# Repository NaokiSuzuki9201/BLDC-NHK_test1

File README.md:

# BLDC-NHK_test1
NHKに向けて製作していたBLDCMD用の基板です。

## 使用素子
・DRV8300D(ゲートドライブ)  
・ACS710(電流検出素子、絶縁)  
・TLP250H?(TP5, LF5?表面実装のやつ)

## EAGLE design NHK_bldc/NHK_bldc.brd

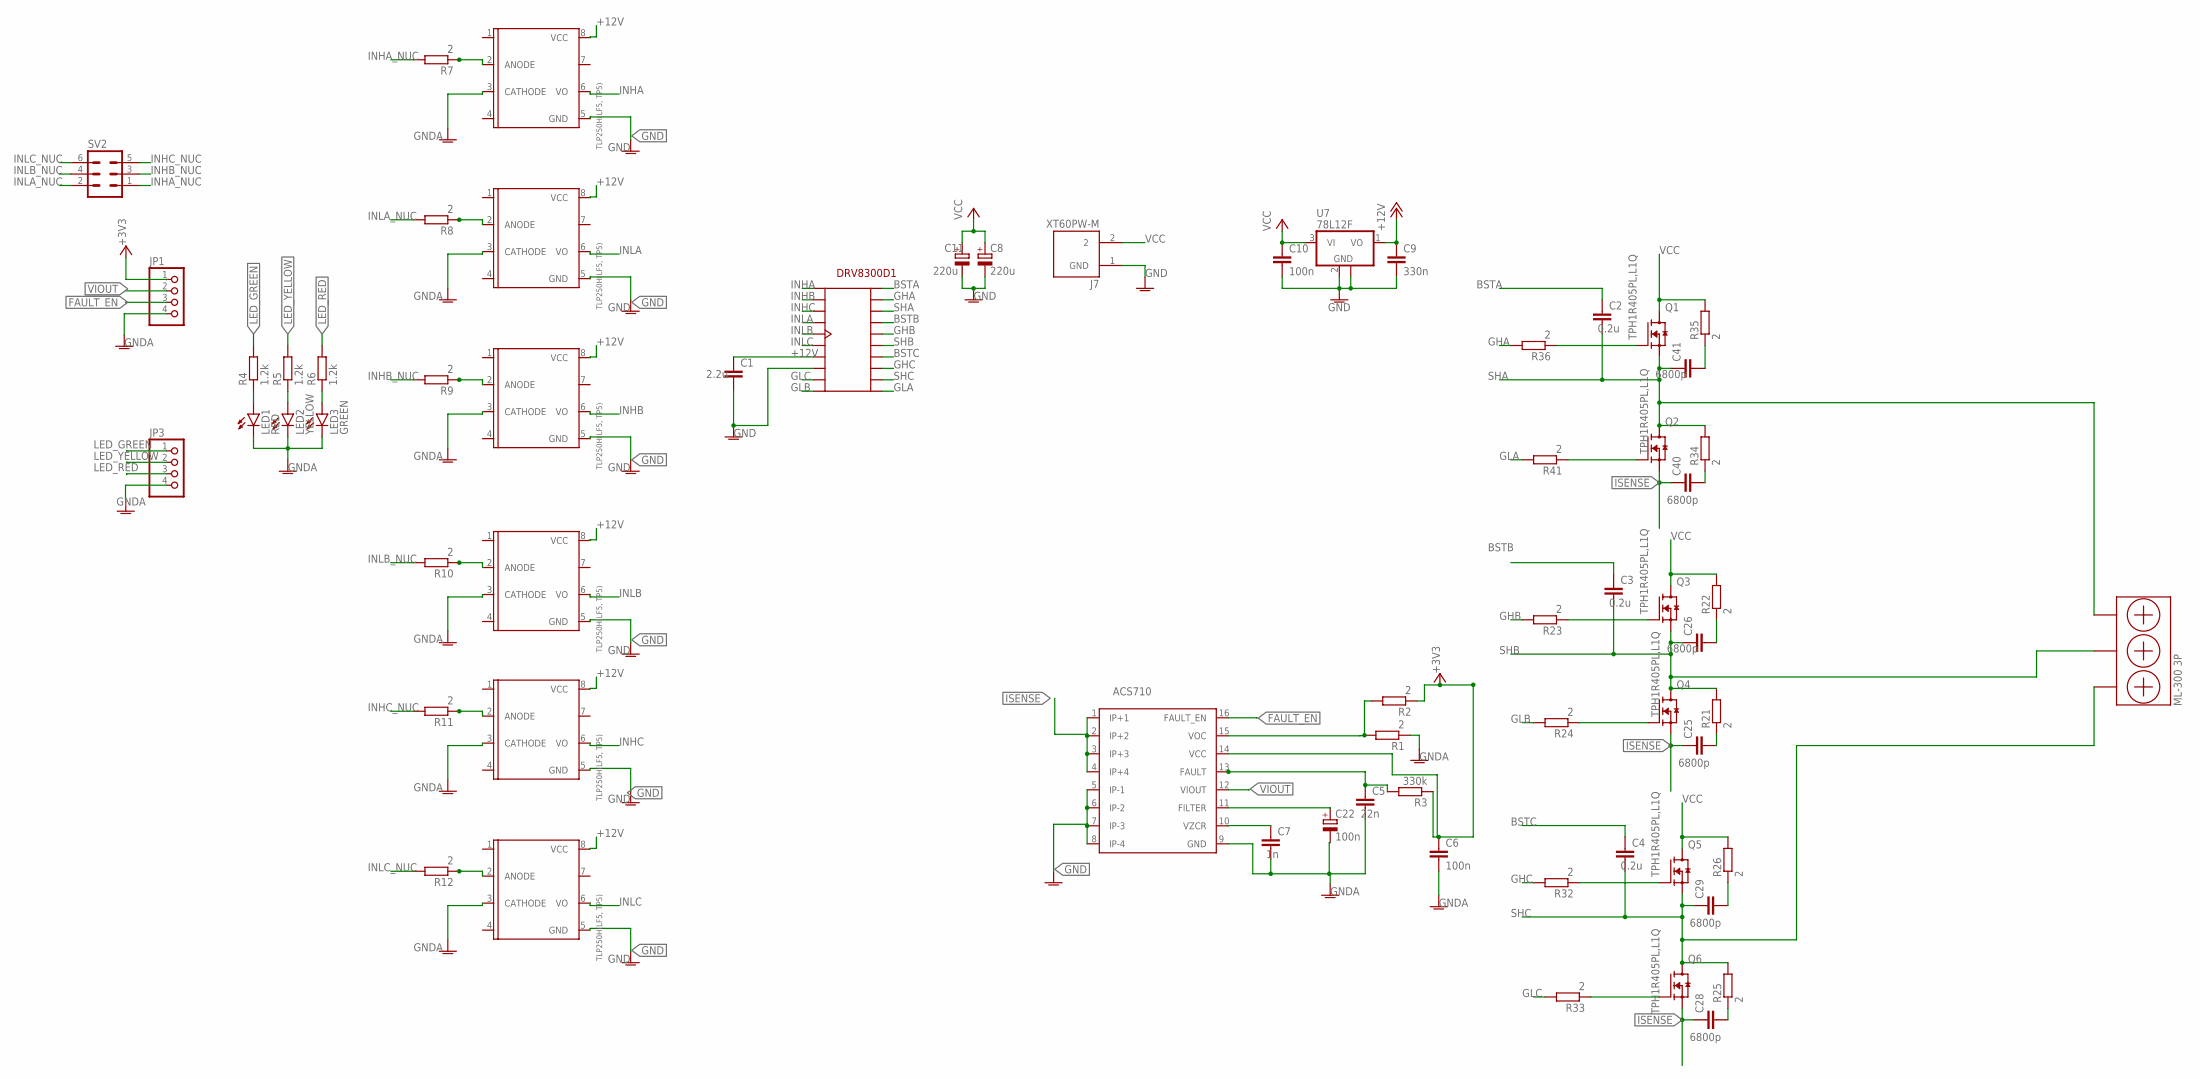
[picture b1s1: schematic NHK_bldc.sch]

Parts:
C1: 2.2u; C1206
C2, C3, C4: 0.2u; C1206
C5: 22n; C0603
C6, C10: 100n; C0603
C7: 1n; C0603
C8, C11: 220u; E5-10,5
C9: 330n; C0603
C22: 100n; E2,5-5
C25, C26, C28, C29, C40, C41: 6800p; C0603
DRV8300D1: DRV8300D
J7: XT60PW-M; AMASS_XT60PW-M
JP1, JP3: PINHD-1X4; 1X04
LED1: RED; CHIP-LED0603
LED2: YELLOW; CHIP-LED0603
LED3: GREEN; CHIP-LED0603
ML-300-3P1: ML-300-3P; ML300-3P
Q1, Q2, Q3, Q4, Q5, Q6: TPH1R405PL,L1Q; SOPADVANCE
R1, R2, R7, R8, R9, R10, R11, R12, R21, R22, R23, R24, R25, R26, R32, R33, R34, R35, R36, R41: 2; R0603
R3: 330k; R0603
R4, R5, R6: 1.2k; R0603
SV2: MA03-2
U7: 78L12F; SOT89
U8, U9, U10, U11, U12, U14: TLP250H(LF5,TP5)
U$1: ACS710

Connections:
+3V3: C6.1, JP1.1, R2.1, R3.1, U$1.14 (VCC)
+12V: C1.1, C9.1, DRV8300D1.GVDD, U7.1 (VO), U8.8 (VCC), U9.8 (VCC), U10.8 (VCC), U11.8 (VCC), U12.8 (VCC), U14.8 (VCC)
AHG1: Q1.4 (G), R36.1
AHG3: Q3.4 (G), R23.1
AHG4: Q5.4 (G), R32.1
ALG1: Q2.4 (G), R41.1
ALG3: Q4.4 (G), R24.1
ALG4: Q6.4 (G), R33.1
BSTA: C2.1, DRV8300D1.BSTA
BSTB: C3.1, DRV8300D1.BSTB
BSTC: C4.1, DRV8300D1.BSTC
FAULT_EN: JP1.3, U$1.16 (FAULT_EN)
GHA: DRV8300D1.GHA, R36.2
GHB: DRV8300D1.GHB, R23.2
GHC: DRV8300D1.GHC, R32.2
GLA: DRV8300D1.GLA, R41.2
GLB: DRV8300D1.GLB, R24.2
GLC: DRV8300D1.GLC, R33.2
GND: C1.2, C8.-, C9.2, C10.2, C11.-, DRV8300D1.GND, J7.1 (GND), U7.2 (GND), U7.2@1 (GND), U8.5 (GND), U9.5 (GND), U10.5 (GND), U11.5 (GND), U12.5 (GND), U14.5 (GND), U$1.5 (IP-1), U$1.6 (IP-2), U$1.7 (IP-3), U$1.8 (IP-4)
GNDA: C5.2, C6.2, C7.2, C22.-, JP1.4, JP3.4, LED1.C, LED2.C, LED3.C, R1.1, U8.3 (CATHODE), U9.3 (CATHODE), U10.3 (CATHODE), U11.3 (CATHODE), U12.3 (CATHODE), U14.3 (CATHODE), U$1.9 (GND)
INHA: DRV8300D1.INHA, U8.6 (VO)
INHA_NUC: R7.2, SV2.1
INHB: DRV8300D1.INHB, U10.6 (VO)
INHB_NUC: R9.2, SV2.3
INHC: DRV8300D1.INHC, U12.6 (VO)
INHC_NUC: R11.2, SV2.5
INLA: DRV8300D1.INLA, U9.6 (VO)
INLA_NUC: R8.2, SV2.2
INLB: DRV8300D1.INLB, U11.6 (VO)
INLB_NUC: R10.2, SV2.4
INLC: DRV8300D1.INLC, U14.6 (VO)
INLC_NUC: R12.2, SV2.6
ISENSE: C25.1, C28.1, C40.1, Q2.1 (S), Q2.2 (S), Q2.3 (S), Q4.1 (S), Q4.2 (S), Q4.3 (S), Q6.1 (S), Q6.2 (S), Q6.3 (S), U$1.1 (IP+1), U$1.2 (IP+2), U$1.3 (IP+3), U$1.4 (IP+4)
LED_GREEN: JP3.1, R4.2
LED_RED: JP3.3, R6.2
LED_YELLOW: JP3.2, R5.2
unnamed: LED1.A, R4.1
unnamed: LED2.A, R5.1
unnamed: R1.2, R2.2, U$1.15 (VOC)
unnamed: C5.1, R3.2, U$1.13 (FAULT)
unnamed: C7.1, U$1.10 (VZCR)
unnamed: LED3.A, R6.1
unnamed: R7.1, U8.2 (ANODE)
unnamed: R8.1, U9.2 (ANODE)
unnamed: R9.1, U10.2 (ANODE)
unnamed: R10.1, U11.2 (ANODE)
unnamed: R11.1, U12.2 (ANODE)
unnamed: R12.1, U14.2 (ANODE)
unnamed: C22.+, U$1.11 (FILTER)
unnamed: C25.2, R21.1
unnamed: C26.2, R22.1
unnamed: C28.2, R25.1
unnamed: C29.2, R26.1
unnamed: C40.2, R34.1
unnamed: C41.2, R35.1
SHA: C2.2, C41.1, DRV8300D1.SHA, ML-300-3P1.P$1, Q1.1 (S), Q1.2 (S), Q1.3 (S), Q2.5 (D), Q2.6 (D), Q2.7 (D), Q2.8 (D), Q2.9 (D), R34.2
SHB: C3.2, C26.1, DRV8300D1.SHB, ML-300-3P1.P$3, Q3.1 (S), Q3.2 (S), Q3.3 (S), Q4.5 (D), Q4.6 (D), Q4.7 (D), Q4.8 (D), Q4.9 (D), R21.2
SHC: C4.2, C29.1, DRV8300D1.SHC, ML-300-3P1.P$5, Q5.1 (S), Q5.2 (S), Q5.3 (S), Q6.5 (D), Q6.6 (D), Q6.7 (D), Q6.8 (D), Q6.9 (D), R25.2
VCC: C8.+, C10.1, C11.+, J7.2, Q1.5 (D), Q1.6 (D), Q1.7 (D), Q1.8 (D), Q1.9 (D), Q3.5 (D), Q3.6 (D), Q3.7 (D), Q3.8 (D), Q3.9 (D), Q5.5 (D), Q5.6 (D), Q5.7 (D), Q5.8 (D), Q5.9 (D), R22.2, R26.2, R35.2, U7.3 (VI)
VIOUT: JP1.2, U$1.12 (VIOUT)

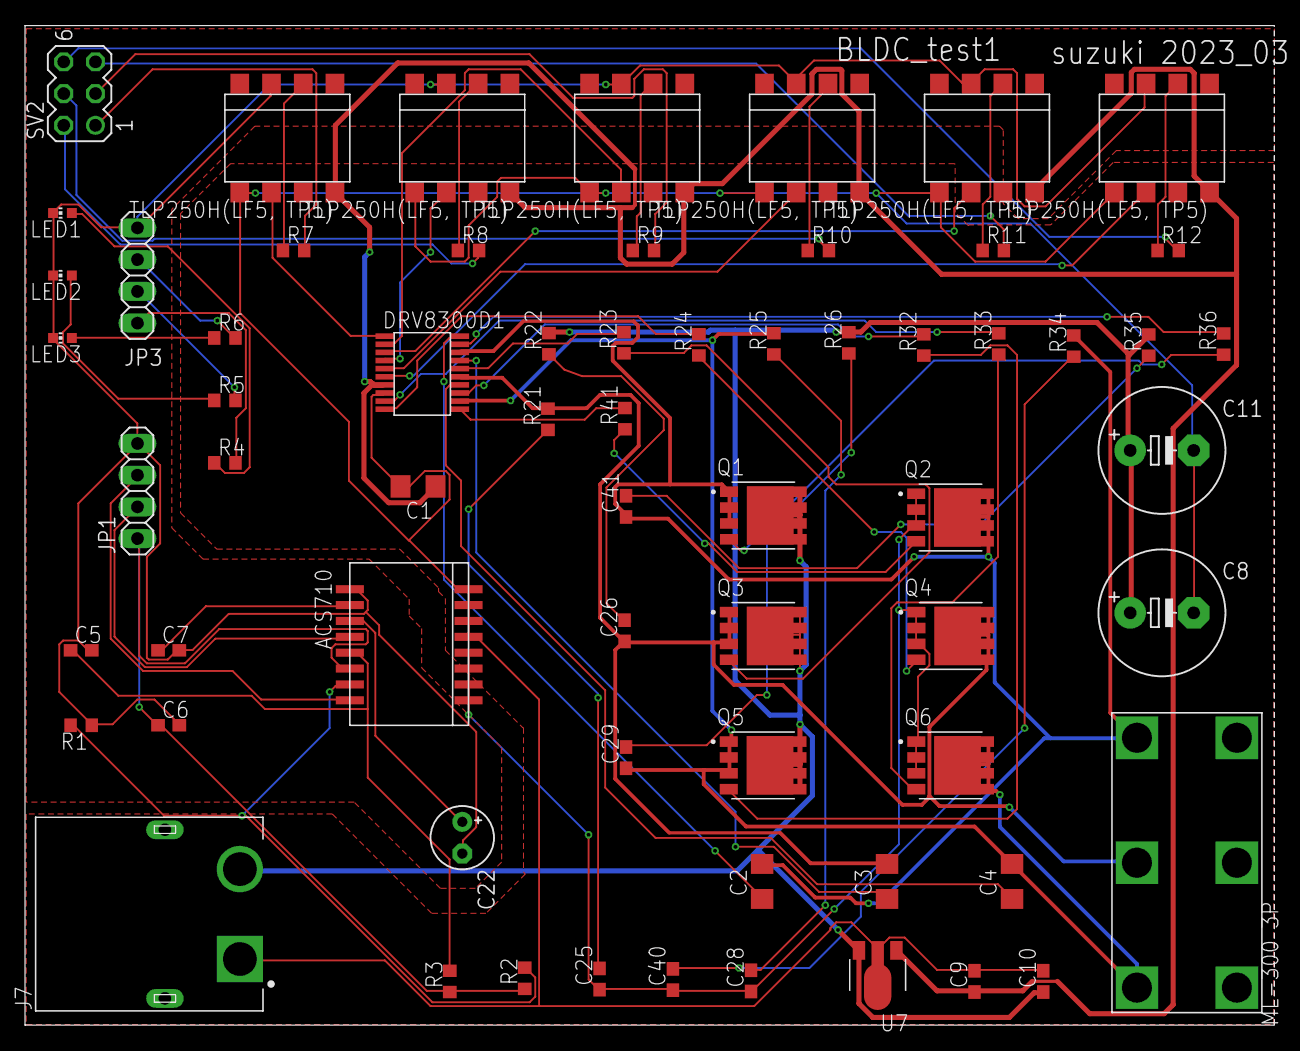
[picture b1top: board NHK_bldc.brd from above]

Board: 2 copper layers, 99.9 x 80.0 mm, 65 parts (0 on the bottom side), 60 nets.
